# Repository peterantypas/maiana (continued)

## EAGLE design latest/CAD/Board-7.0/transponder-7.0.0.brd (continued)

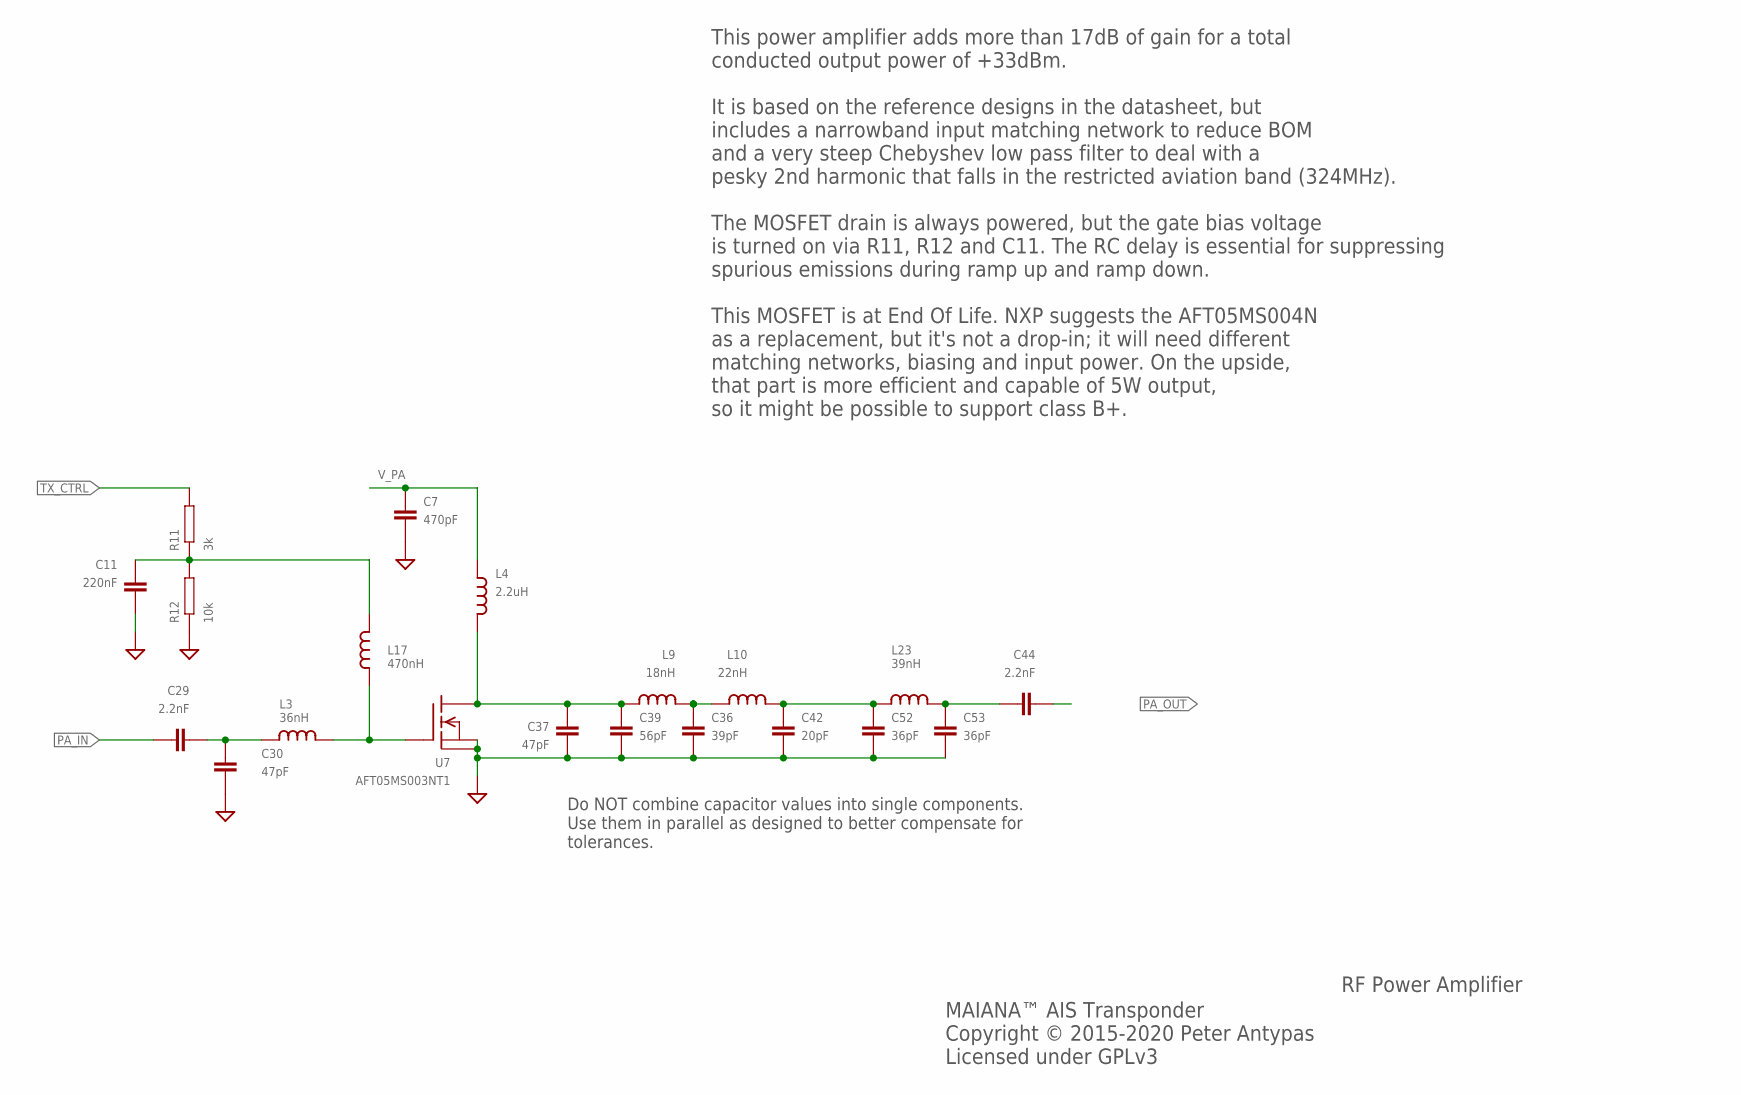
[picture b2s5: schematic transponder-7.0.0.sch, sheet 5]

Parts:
C7: 470pF; 0603; PARTNO GRM1885C1H471JA01D
C11: 220nF; 0603; PARTNO C0603C224K4RECAUTO
C29, C44: 2.2nF; 0603; PARTNO GRM1885C1H222JA01J
C30, C37: 47pF; 0603; PARTNO GRM1885C1H470JA01J
C36: 39pF; 0603; PARTNO GRM1885C1H390JA01D
C39: 56pF; 0603; PARTNO GRM1885C1H560JA01D
C42: 20pF; 0603; PARTNO GRM1885C1H200JA01D
C52, C53: 36pF; 0603; PARTNO 06035A360JAT2A
L3: 36nH; 0603; PARTNO LQW18AN36NG00D
L4: 2.2uH; 0805; PARTNO BRC2012T2R2MD
L9: 18nH; 0603; PARTNO LQW18AN18NG00D
L10: 22nH; 0603; PARTNO LQW18AN22NJ00D
L17: 470nH; 0603; PARTNO HK1608R47J-T
L23: 39nH; 0603; PARTNO LQW18AN39NG00D
R11: 3k; 0603; PARTNO RC0603JR-073KL
R12: 10k; 0603; PARTNO RC0603JR-0710KL
U7: AFT05MS003NT1; SOT-89; PARTNO AFT05MS003NT1

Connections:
GND: C7.P$2 (2), C11.P$2 (2), C30.P$2 (2), C36.P$2 (2), C37.P$2 (2), C39.P$2 (2), C42.P$2 (2), C52.P$2 (2), C53.P$2 (2), R12.P$1, U7.2 (S), U7.2@1 (PAD); also elsewhere on the board
unnamed: C11.P$1 (1), L17.P$2 (2), R11.P$1, R12.P$2
unnamed: C37.P$1 (1), C39.P$1 (1), L4.P$2 (2), L9.P$1 (1), U7.3 (D)
unnamed: L3.P$2 (2), L17.P$1 (1), U7.1 (G)
unnamed: C36.P$1 (1), L9.P$2 (2), L10.P$1 (1)
unnamed: C29.P$2 (2), C30.P$1 (1), L3.P$1 (1)
unnamed: C42.P$1 (1), C52.P$1 (1), L10.P$2 (2), L23.P$1 (1)
unnamed: C44.P$1 (1), C53.P$1 (1), L23.P$2 (2)
PA_IN: C29.P$1 (1); also elsewhere on the board
PA_OUT: C44.P$2 (2); also elsewhere on the board
TX_CTRL: R11.P$2; also elsewhere on the board
V_PA: C7.P$1 (1), L4.P$1 (1); also elsewhere on the board

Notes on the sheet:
RF Power Amplifier
MAIANA™ AIS Transponder Copyright © 2015-2020 Peter Antypas Licensed under GPLv3
This power amplifier adds more than 17dB of gain for a total conducted output power of +33dBm. It is based on the reference designs in the datasheet, but includes a narrowband input matching network to reduce BOM and a very steep Chebyshev low pass filter to deal with a pesky 2nd harmonic that fall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
Do NOT combine capacitor values into single components. Use them in parallel as designed to better compensate for tolerances.

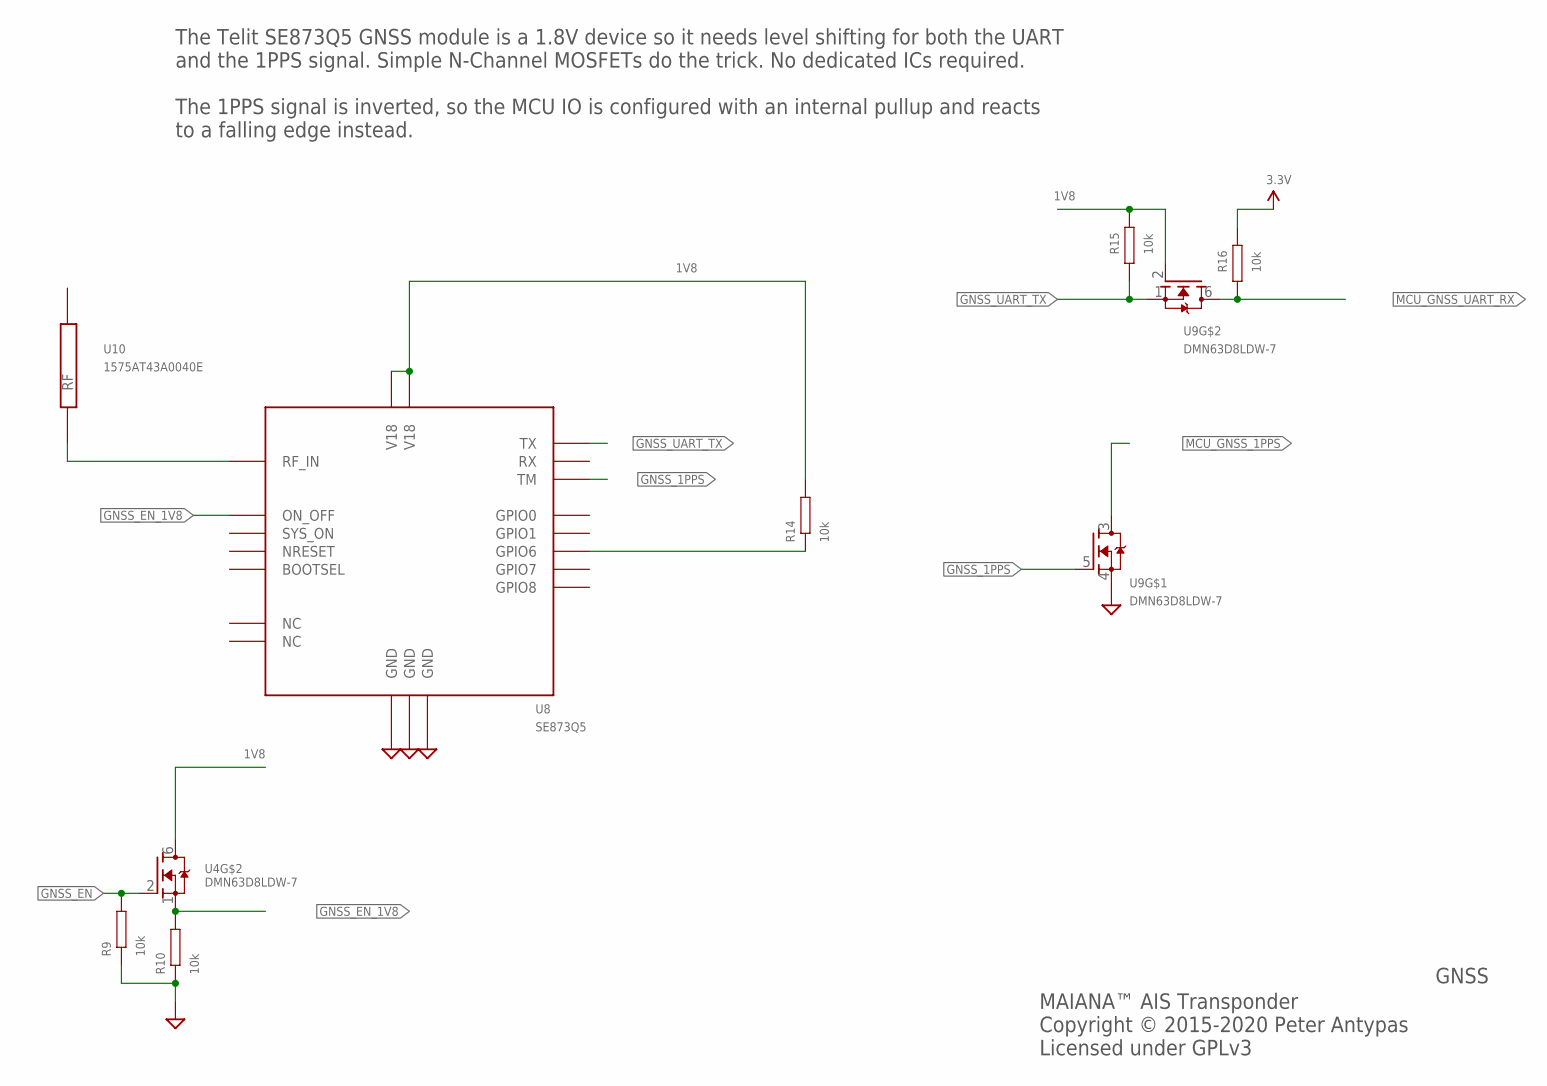
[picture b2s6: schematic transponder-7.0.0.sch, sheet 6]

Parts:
R9, R10, R14, R15, R16: 10k; 0603; PARTNO RC0603JR-0710KL
U4, U9: DMN63D8LDW-7; SOT363; PARTNO DMN63D8LDW-7
U8: SE873Q5; SE873; PARTNO SE873Q5
U10: 1575AT43A0040E; PARTNO 1575AT43A0040E

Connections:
1V8: R14.P$2, R15.P$2, U4.6 (D), U8.P$3 (V18), U8.P$19 (V18), U9.2 (G); also elsewhere on the board
3.3V: R16.P$2; also elsewhere on the board
GND: R9.P$1, R10.P$1, U8.P$2 (GND), U8.P$10 (GND), U8.P$20 (GND), U9.4 (S); also elsewhere on the board
GNSS_1PPS: U8.P$11 (TM), U9.5 (G)
GNSS_EN: R9.P$2, U4.2 (G); also elsewhere on the board
GNSS_EN_1V8: R10.P$2, U4.1 (S), U8.P$6 (ON_OFF)
GNSS_UART_TX: R15.P$1, U8.P$15 (TX), U9.1 (S)
MCU_GNSS_1PPS: U9.3 (D); also elsewhere on the board
MCU_GNSS_UART_RX: R16.P$1, U9.6 (D); also elsewhere on the board
unnamed: U8.P$1 (RF_IN), U10.P$1 (RF)
unnamed: R14.P$1, U8.P$13 (GPIO6)

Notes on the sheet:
GNSS
MAIANA™ AIS Transponder Copyright © 2015-2020 Peter Antypas Licensed under GPLv3
The Telit SE873Q5 GNSS module is a 1.8V device so it needs level shifting for both the UART and the 1PPS signal. Simple N-Channel MOSFETs do the trick. No dedicated ICs required. The 1PPS signal is inverted, so the MCU IO is configured with an internal pullup and reacts to a falling edge instead.

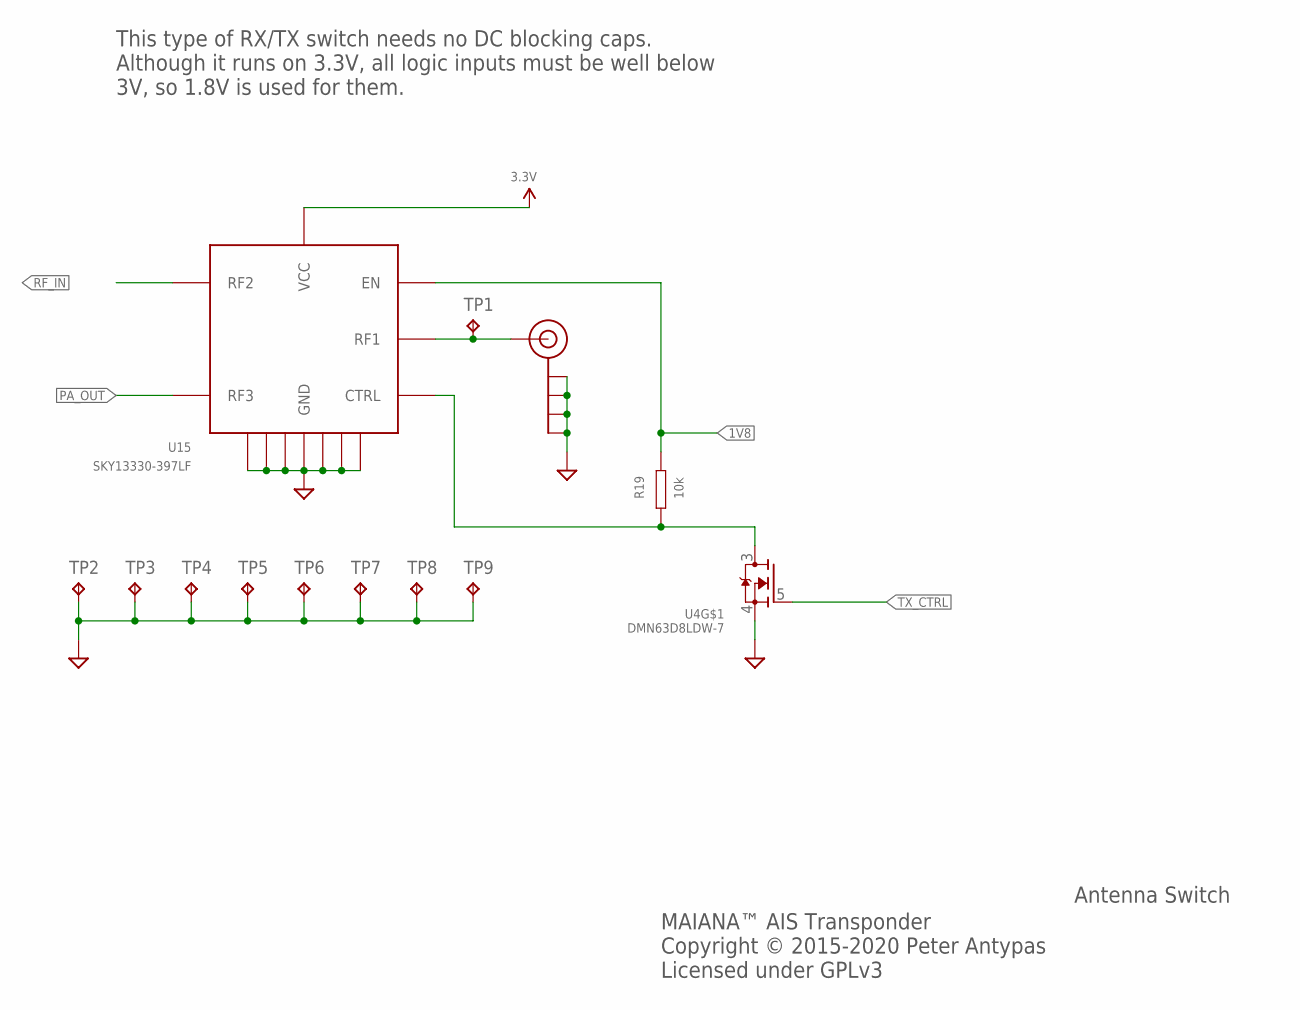
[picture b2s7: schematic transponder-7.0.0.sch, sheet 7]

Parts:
J$1: SMA_EDGE; SMA-EDGE
R19: 10k; 0603; PARTNO RC0603JR-0710KL
TP1: TPTP10R; TP10R
TP2, TP3, TP4, TP5, TP6, TP7, TP8, TP9: TPTP08R; TP08R
U4: DMN63D8LDW-7; SOT363; PARTNO DMN63D8LDW-7
U15: SKY13330-397LF; QFN12; PARTNO SKY13330-397LF

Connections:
1V8: R19.P$2, U15.P$8 (EN); also elsewhere on the board
3.3V: U15.P$9 (VCC); also elsewhere on the board
GND: J$1.GND@0 (GND), J$1.GND@1 (GND), J$1.GND@2 (GND), J$1.GND@3 (GND), TP2.TP, TP3.TP, TP4.TP, TP5.TP, TP6.TP, TP7.TP, TP8.TP, TP9.TP, U4.4 (S), U15.P$1 (GND), U15.P$3 (GND), U15.P$4 (GND), U15.P$6 (GND), U15.P$10 (GND), U15.P$12 (GND), U15.P$13 (GND); also elsewhere on the board
unnamed: J$1.SIG (SIGNAL), TP1.TP, U15.P$2 (RF1)
PA_OUT: U15.P$5 (RF3); also elsewhere on the board
RF_IN: U15.P$11 (RF2); also elsewhere on the board
RX_EN: R19.P$1, U4.3 (D), U15.P$7 (CTRL)
TX_CTRL: U4.5 (G); also elsewhere on the board

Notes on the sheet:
Antenna Switch
MAIANA™ AIS Transponder Copyright © 2015-2020 Peter Antypas Licensed under GPLv3
This type of RX/TX switch needs no DC blocking caps. Although it runs on 3.3V, all logic inputs must be well below 3V, so 1.8V is used for them.

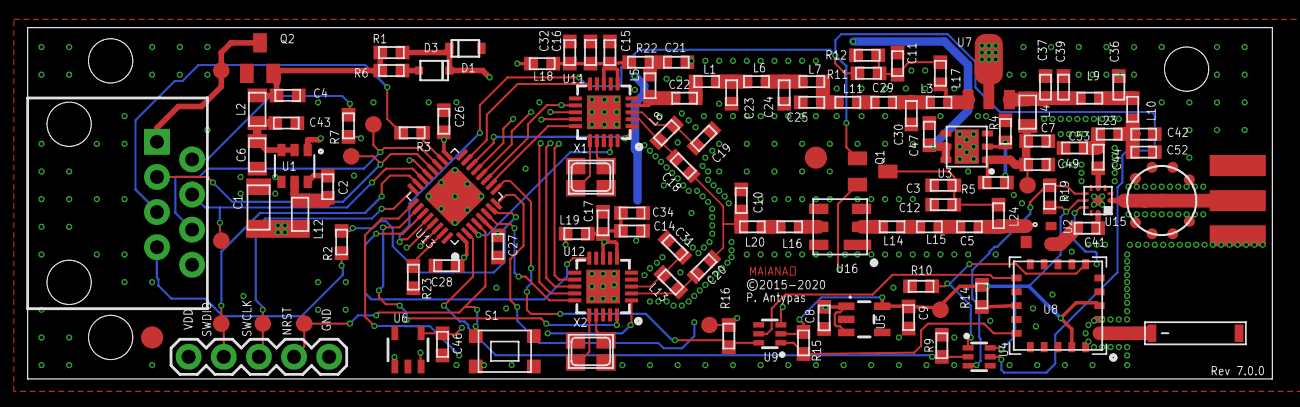
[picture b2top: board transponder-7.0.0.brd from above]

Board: 4 copper layers, 90.0 x 25.4 mm, 130 parts (1 on the bottom side), 84 nets.

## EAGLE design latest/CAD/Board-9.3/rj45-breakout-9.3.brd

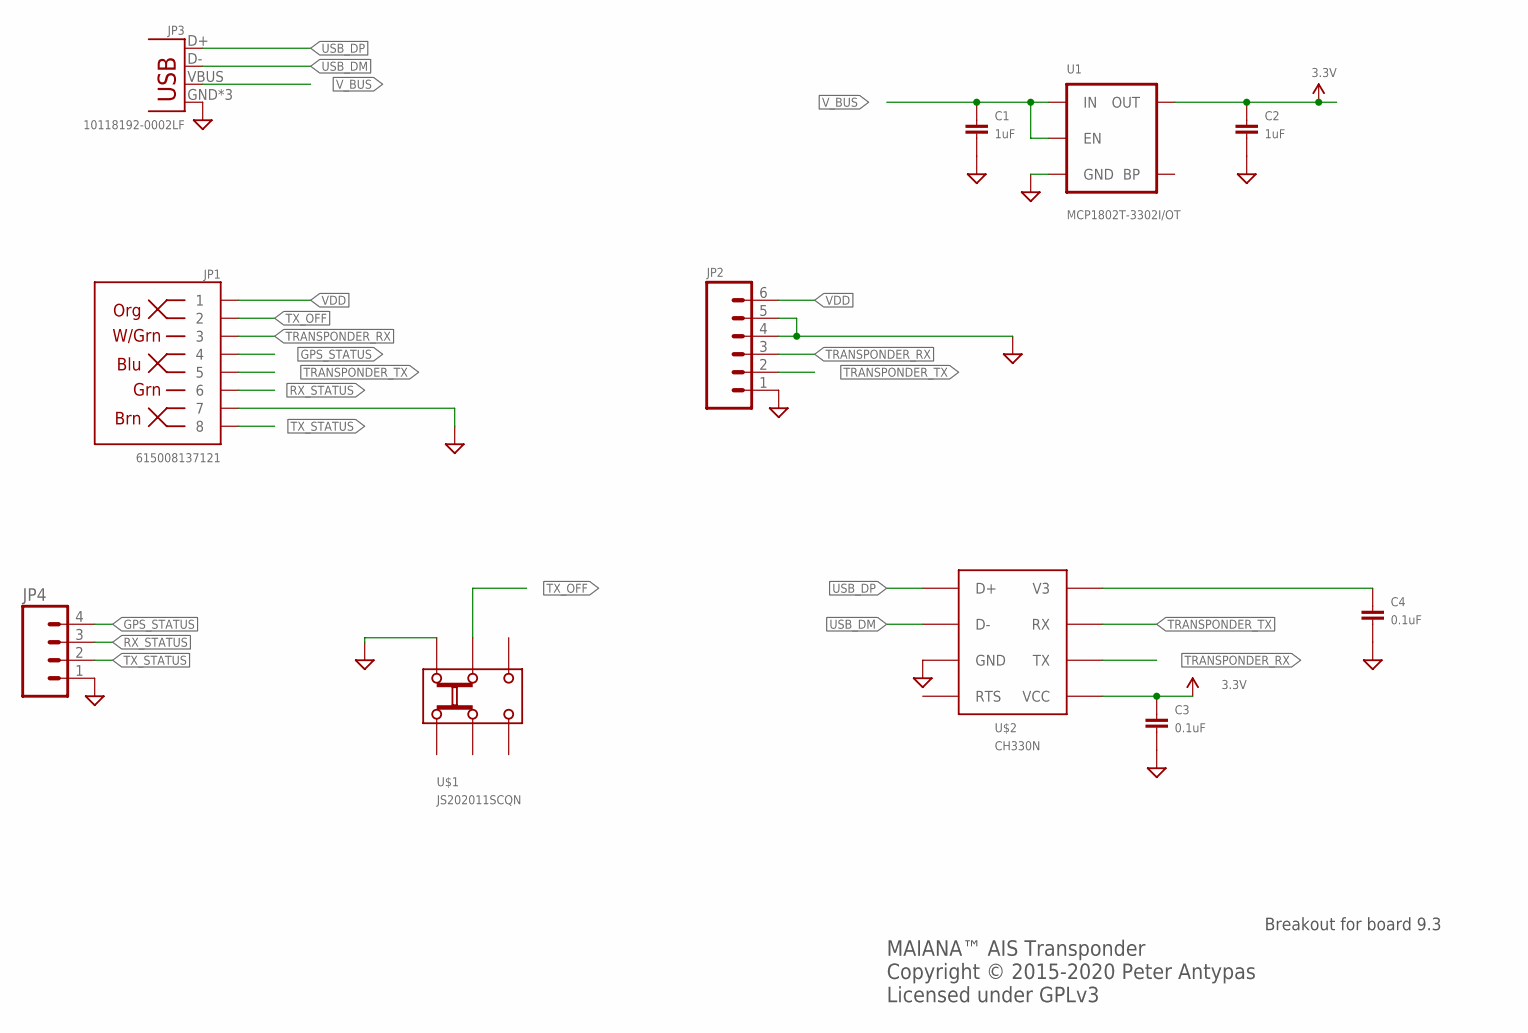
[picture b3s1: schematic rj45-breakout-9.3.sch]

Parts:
C1, C2: 1uF; 0603
C3, C4: 0.1uF; 0603
JP1: 615008137121; RJ45-8
JP2: M06SILK_FEMALE_PTH; 1X06
JP3: 10118192-0002LF; USB-MICROB
JP4: M04PTH; 1X04
U1: MCP1802T-3302I/OT; SOT23-5
U$1: JS202011SCQN; DPDT-SMD
U$2: CH330N; SOIC-8

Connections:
3.3V: C2.P$1, C3.P$1, U1.5 (OUT), U$2.5 (VCC)
GND: C1.P$2, C2.P$2, C3.P$2, C4.P$2, JP1.7, JP2.1, JP2.4, JP2.5, JP3.GND, JP3.MT1 (GND), JP3.MT2 (GND), JP4.1, U1.2 (GND), U$1.P$6, U$2.3 (GND)
GPS_STATUS: JP1.4, JP4.4
unnamed: C4.P$1, U$2.8 (V3)
RX_STATUS: JP1.6, JP4.3
TRANSPONDER_RX: JP1.3, JP2.3, U$2.6 (TX)
TRANSPONDER_TX: JP1.5, JP2.2, U$2.7 (RX)
TX_OFF: JP1.2, U$1.P$5
TX_STATUS: JP1.8, JP4.2
USB_DM: JP3.D-, U$2.2 (D-)
USB_DP: JP3.D+, U$2.1 (D+)
VDD: JP1.1, JP2.6
V_BUS: C1.P$1, JP3.VBUS, U1.1 (IN), U1.3 (EN)

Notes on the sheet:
MAIANA™ AIS Transponder Copyright © 2015-2020 Peter Antypas Licensed under GPLv3
Breakout for board 9.3

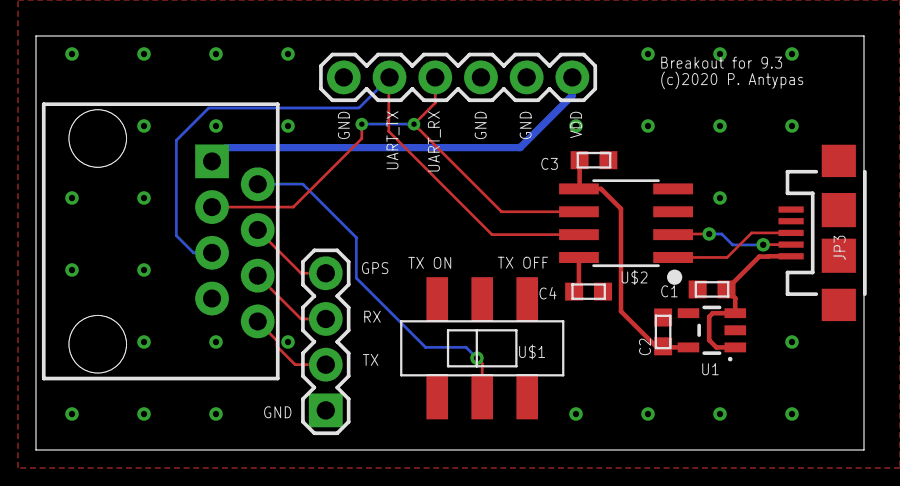
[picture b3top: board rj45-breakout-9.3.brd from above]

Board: 2 copper layers, 46.0 x 23.0 mm, 11 parts (0 on the bottom side), 13 nets.

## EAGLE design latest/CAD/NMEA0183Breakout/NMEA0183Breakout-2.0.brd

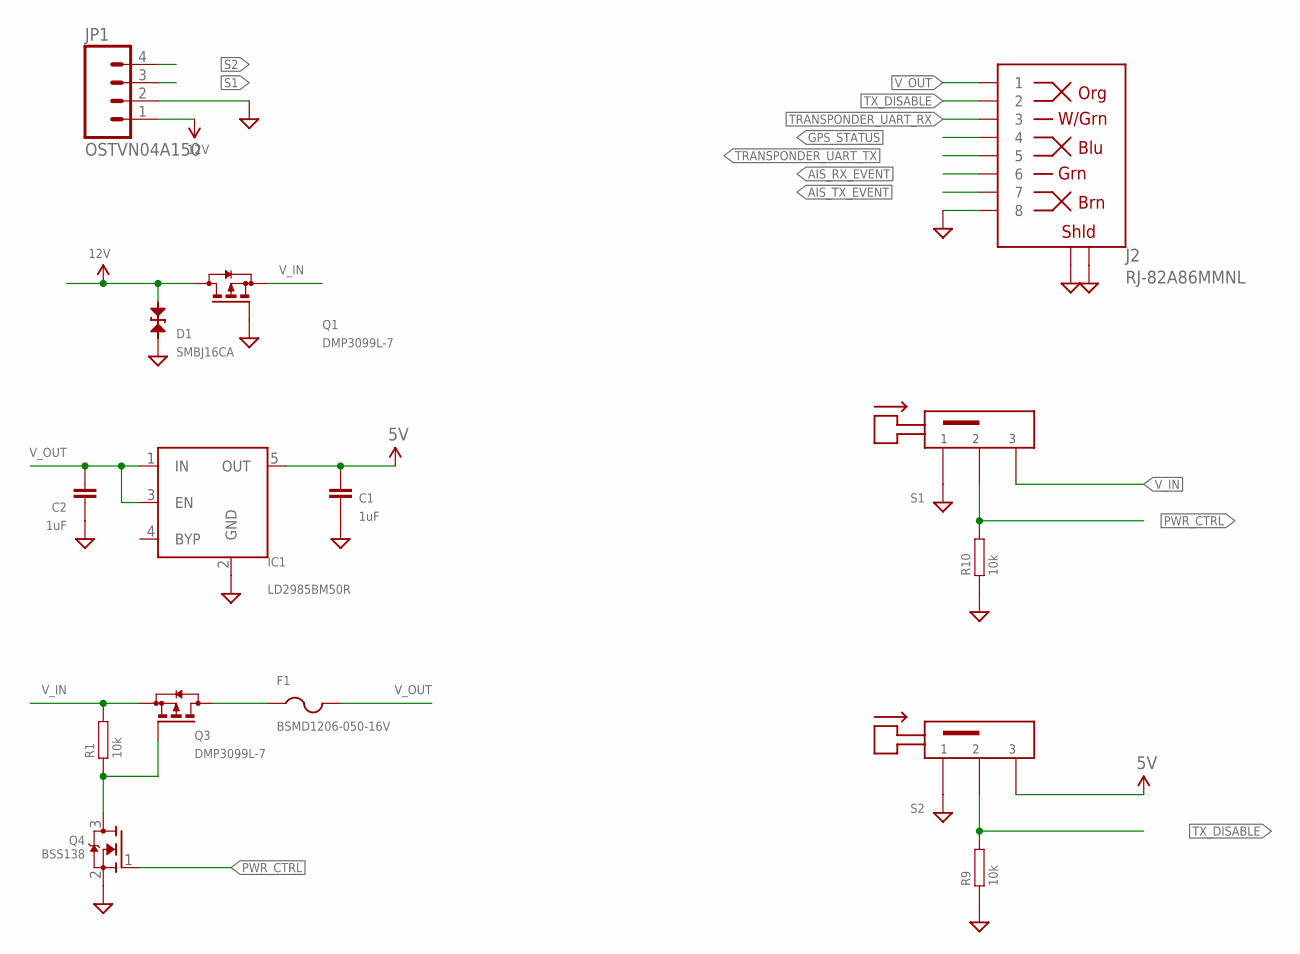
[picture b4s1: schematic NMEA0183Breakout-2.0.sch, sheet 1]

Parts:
C1, C2: 1uF; 0603
D1: SMBJ16CA; SMB-BIDIR
F1: BSMD1206-050-16V; R1206
IC1: LD2985BM50R; SOT23-5
J2: RJ-82A86MMNL
JP1: OSTVN04A150; 1X04
Q1, Q3: DMP3099L-7; SOT23
Q4: BSS138; SOT23
R1, R9, R10: 10k; 0603
S1, S2: LC1258XXNP

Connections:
5V: C1.P$1 (1), IC1.5 (OUT), S2.P$3 (3); also elsewhere on the board
12V: D1.A, JP1.1, Q1.3 (D)
AIS_RX_EVENT: J2.P$6 (6); also elsewhere on the board
AIS_TX_EVENT: J2.P$7 (7); also elsewhere on the board
GND: C1.P$2 (2), C2.P$2 (2), D1.C, IC1.2 (GND), J2.P$8 (8), J2.P$9 (SHLD), J2.P$10 (SHLD), J2.P$11 (SHLD), J2.P$12 (SHLD), JP1.2, Q1.1 (G), Q4.2 (S), R9.P$1, R10.P$1, S1.P$1 (1), S2.P$1 (1); also elsewhere on the board
GPS_STATUS: J2.P$4 (4); also elsewhere on the board
unnamed: Q3.1 (G), Q4.3 (D), R1.P$1
unnamed: F1.1, Q3.3 (D)
PWR_CTRL: Q4.1 (G), R10.P$2, S1.P$2 (2)
S1: JP1.3; also elsewhere on the board
S2: JP1.4; also elsewhere on the board
TRANSPONDER_UART_RX: J2.P$3 (3); also elsewhere on the board
TRANSPONDER_UART_TX: J2.P$5 (5); also elsewhere on the board
TX_DISABLE: J2.P$2 (2), R9.P$2, S2.P$2 (2); also elsewhere on the board
V_IN: Q1.2 (S), Q3.2 (S), R1.P$2, S1.P$3 (3)
V_OUT: C2.P$1 (1), F1.2, IC1.1 (IN), IC1.3 (EN), J2.P$1 (1)

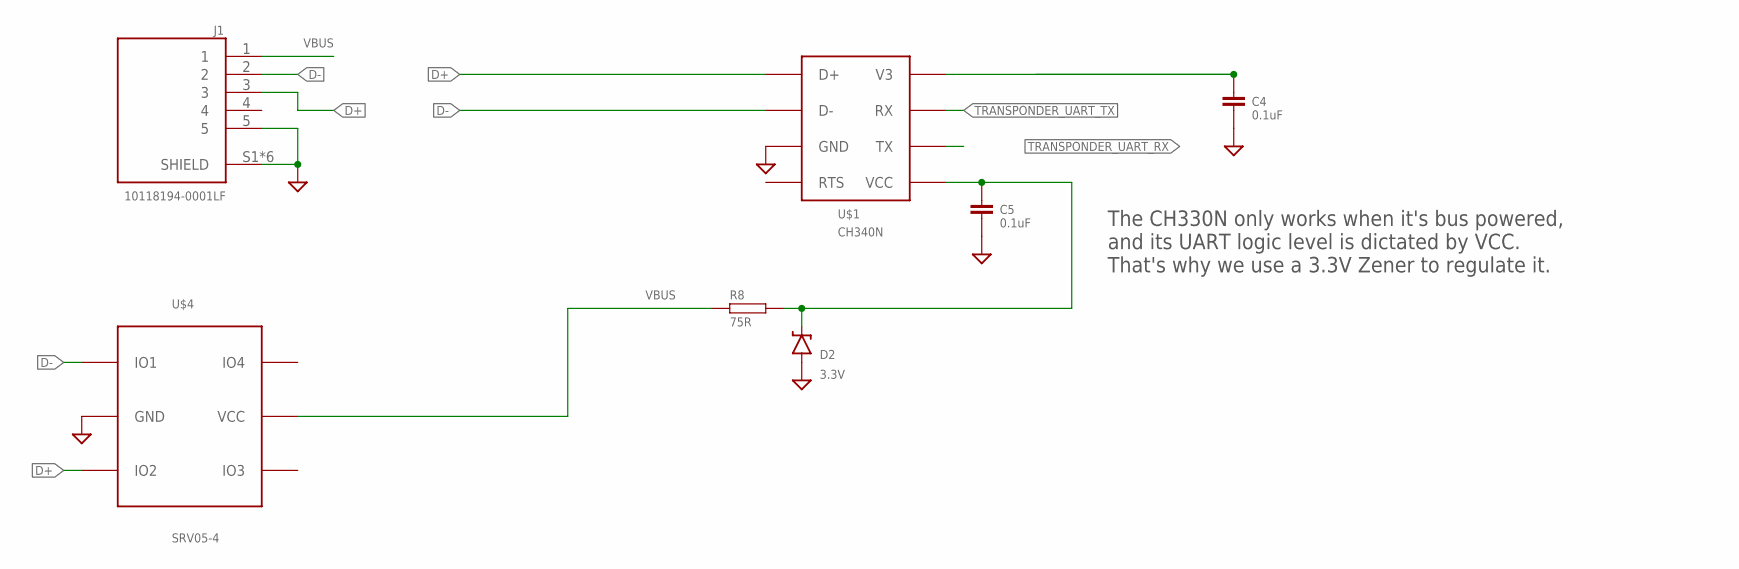
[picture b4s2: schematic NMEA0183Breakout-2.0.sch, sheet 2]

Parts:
C4, C5: 0.1uF; 0603
D2: 3.3V; SOD-323
J1: 10118194-0001LF; AMPHENOL_10118194-0001LF
R8: 75R; 0603
U$1: CH340N; SOIC-8; PARTNO CH340N
U$4: SRV05-4; SOT23-6

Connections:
D+: J1.3, U$1.1 (D+), U$4.3 (IO2)
D-: J1.2, U$1.2 (D-), U$4.1 (IO1)
GND: C4.P$2 (2), C5.P$2 (2), D2.A, J1.5, J1.S1 (SHIELD), J1.S2 (SHIELD), J1.S3 (SHIELD), J1.S4 (SHIELD), J1.S5 (SHIELD), J1.S6 (SHIELD), U$1.3 (GND), U$4.2 (GND); also elsewhere on the board
unnamed: C4.P$1 (1), U$1.8 (V3)
unnamed: C5.P$1 (1), D2.C, R8.P$2, U$1.5 (VCC)
TRANSPONDER_UART_RX: U$1.6 (TX); also elsewhere on the board
TRANSPONDER_UART_TX: U$1.7 (RX); also elsewhere on the board
VBUS: J1.1, R8.P$1, U$4.5 (VCC)

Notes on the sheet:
The CH330N only works when it's bus powered, and its UART logic level is dictated by VCC. That's why we use a 3.3V Zener to regulate it.

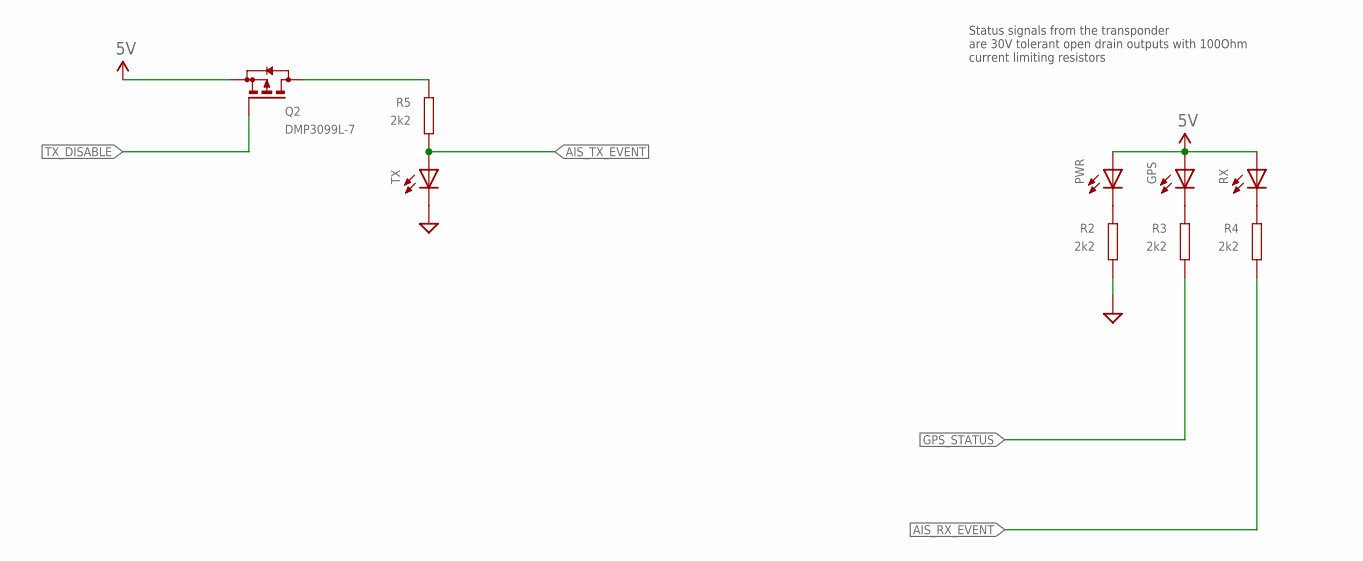
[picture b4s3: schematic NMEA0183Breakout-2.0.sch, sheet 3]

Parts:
GPS: LEDCHIPLED_1206; CHIPLED_1206; PARTNO TJ-S3216CL9T5ALC2G-A5
PWR: LEDCHIPLED_1206; CHIPLED_1206; PARTNO TJ-S3216CL9T5ALC2G-A5
Q2: DMP3099L-7; SOT23
R2, R3, R4, R5: 2k2; 0603
RX: LEDCHIPLED_1206; CHIPLED_1206; PARTNO TJ-S3216CL9T5ALC2G-A5
TX: LEDCHIPLED_1206; CHIPLED_1206; PARTNO TJ-S3216CL9T5ALC2G-A5

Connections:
5V: GPS.A, PWR.A, Q2.2 (S), RX.A; also elsewhere on the board
AIS_RX_EVENT: R4.P$2; also elsewhere on the board
AIS_TX_EVENT: R5.P$2, TX.A; also elsewhere on the board
GND: R2.P$2, TX.C; also elsewhere on the board
GPS_STATUS: R3.P$2; also elsewhere on the board
unnamed: PWR.C, R2.P$1
unnamed: GPS.C, R3.P$1
unnamed: R4.P$1, RX.C
unnamed: Q2.3 (D), R5.P$1
TX_DISABLE: Q2.1 (G); also elsewhere on the board

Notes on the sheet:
Status signals from the transponder are 30V tolerant open drain outputs with 100Ohm current limiting resistors

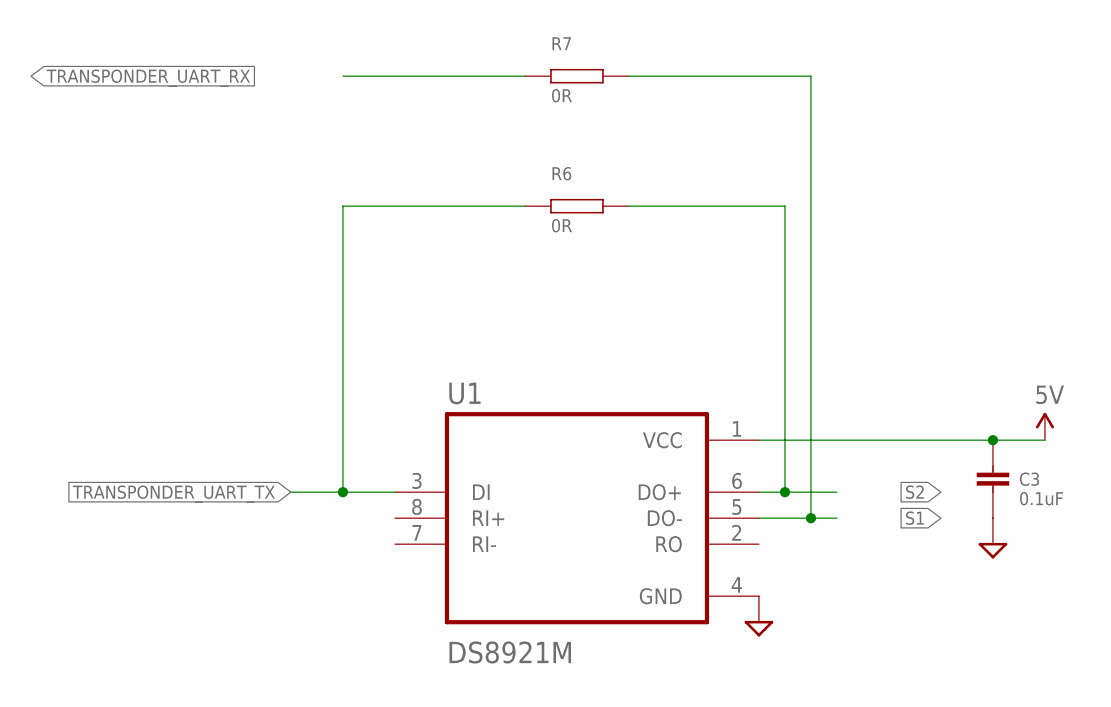
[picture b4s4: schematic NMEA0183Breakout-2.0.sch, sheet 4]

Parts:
C3: 0.1uF; 0603
R6, R7: 0R; 0603
U1: DS8921M; SOIC127P599X175-8N

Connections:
5V: C3.P$1 (1), U1.1 (VCC); also elsewhere on the board
GND: C3.P$2 (2), U1.4 (GND); also elsewhere on the board
S1: R7.P$2, U1.5 (DO-); also elsewhere on the board
S2: R6.P$2, U1.6 (DO+); also elsewhere on the board
TRANSPONDER_UART_RX: R7.P$1; also elsewhere on the board
TRANSPONDER_UART_TX: R6.P$1, U1.3 (DI); also elsewhere on the board

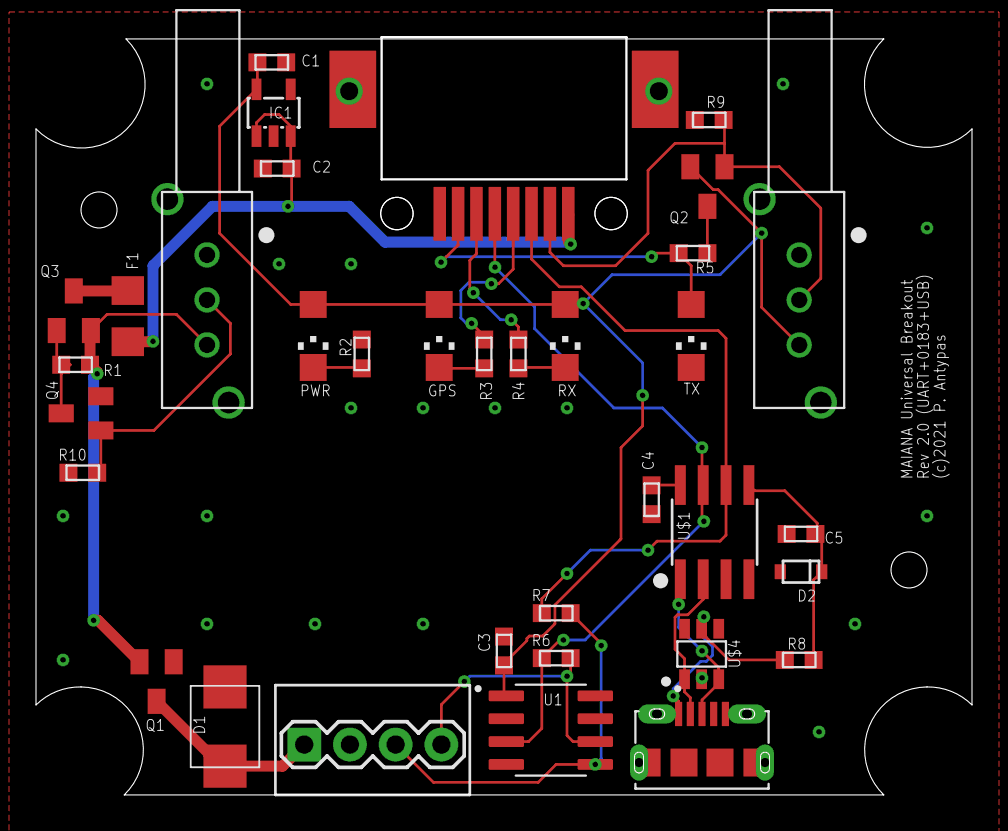
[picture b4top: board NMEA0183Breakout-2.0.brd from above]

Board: 2 copper layers, 52.0 x 42.0 mm, 35 parts (0 on the bottom side), 25 nets.

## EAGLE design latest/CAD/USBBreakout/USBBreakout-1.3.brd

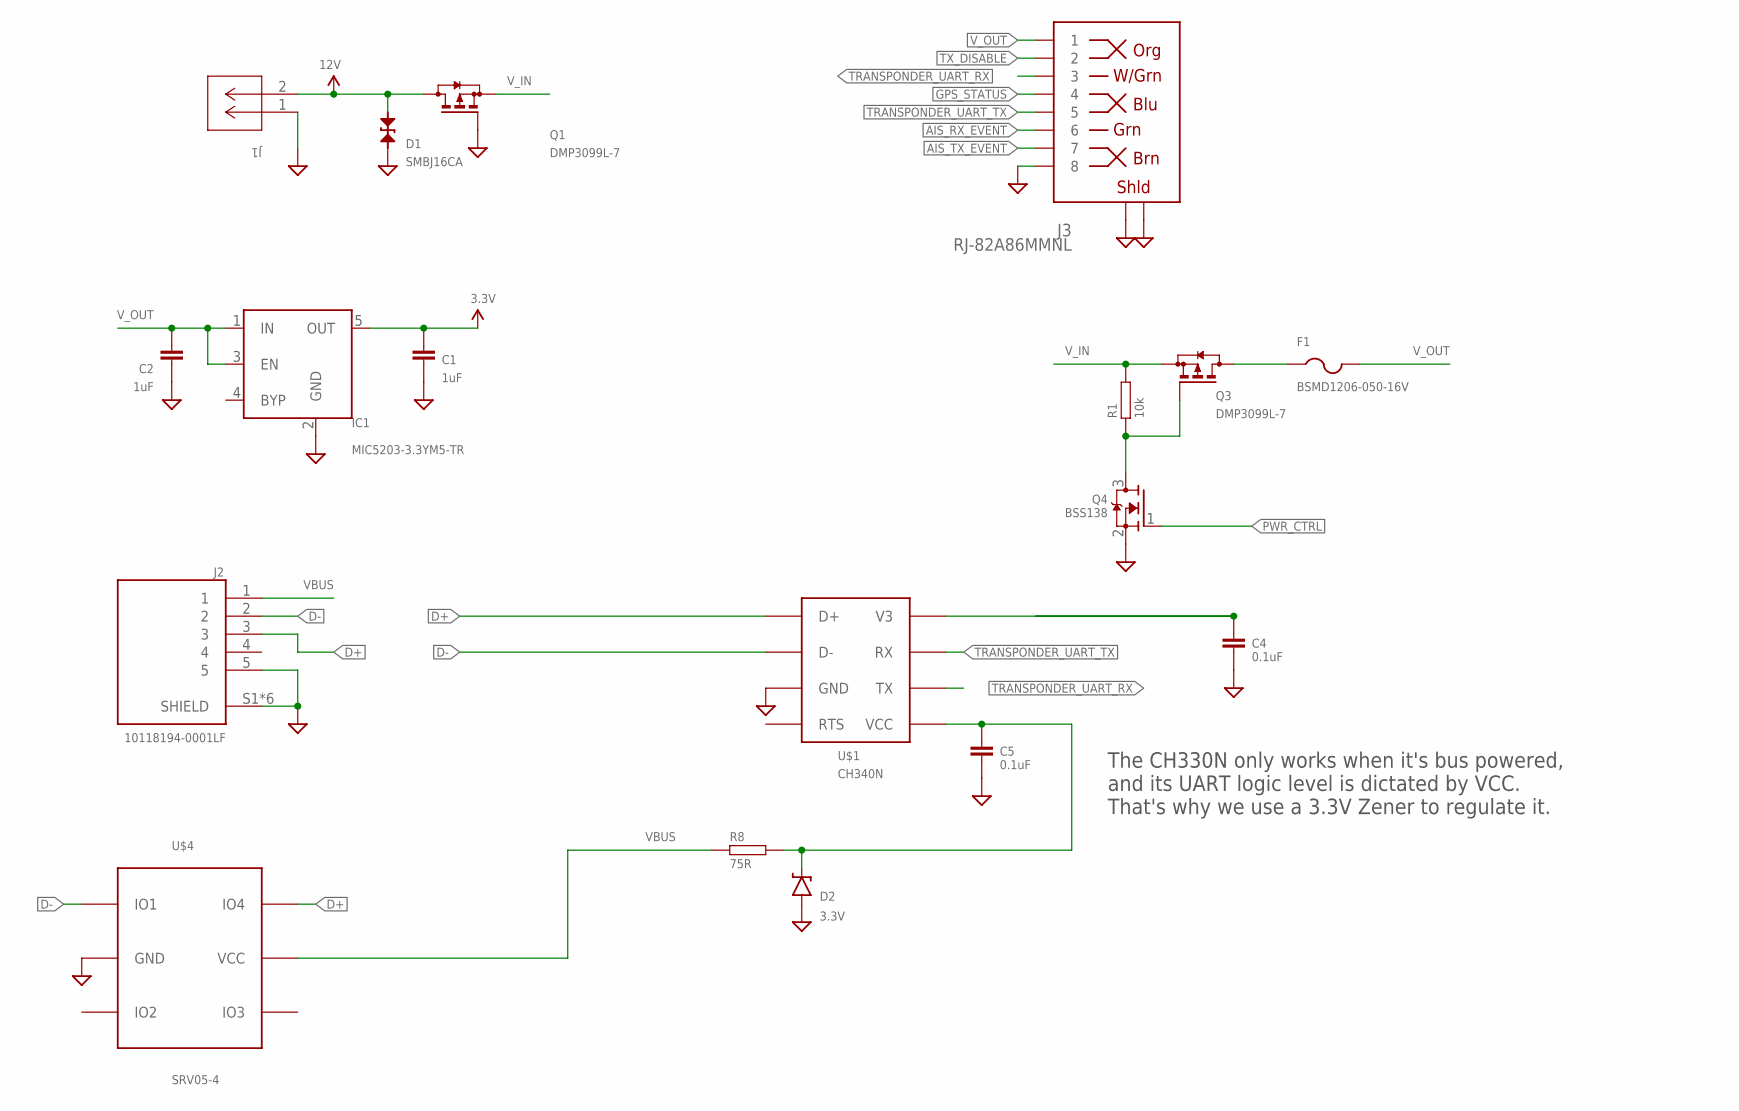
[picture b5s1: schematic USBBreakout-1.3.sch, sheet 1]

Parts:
C1, C2: 1uF; 0603
C4, C5: 0.1uF; 0603
D1: SMBJ16CA; SMB-BIDIR
D2: 3.3V; SOD-323
F1: BSMD1206-050-16V; R1206
IC1: MIC5203-3.3YM5-TR; SOT23-5
J1: OSTVN02A150; CONN_OSTVN02A150_OST
J2: 10118194-0001LF; AMPHENOL_10118194-0001LF
J3: RJ-82A86MMNL
Q1, Q3: DMP3099L-7; SOT23
Q4: BSS138; SOT23
R1: 10k; 0603
R8: 75R; 0603
U$1: CH340N; SOIC-8; PARTNO CH340N
U$4: SRV05-4; SOT23-6

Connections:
3.3V: C1.P$1 (1), IC1.5 (OUT); also elsewhere on the board
12V: D1.A, J1.2, Q1.3 (D)
AIS_RX_EVENT: J3.P$6 (6); also elsewhere on the board
AIS_TX_EVENT: J3.P$7 (7); also elsewhere on the board
D+: J2.3, U$1.1 (D+), U$4.6 (IO4)
D-: J2.2, U$1.2 (D-), U$4.1 (IO1)
GND: C1.P$2 (2), C2.P$2 (2), C4.P$2 (2), C5.P$2 (2), D1.C, D2.A, IC1.2 (GND), J1.1, J2.5, J2.S1 (SHIELD), J2.S2 (SHIELD), J2.S3 (SHIELD), J2.S4 (SHIELD), J2.S5 (SHIELD), J2.S6 (SHIELD), J3.P$8 (8), J3.P$9 (SHLD), J3.P$10 (SHLD), J3.P$11 (SHLD), J3.P$12 (SHLD), Q1.1 (G), Q4.2 (S), U$1.3 (GND), U$4.2 (GND); also elsewhere on the board
GPS_STATUS: J3.P$4 (4); also elsewhere on the board
unnamed: C4.P$1 (1), U$1.8 (V3)
unnamed: Q3.1 (G), Q4.3 (D), R1.P$1
unnamed: F1.1, Q3.3 (D)
unnamed: C5.P$1 (1), D2.C, R8.P$2, U$1.5 (VCC)
PWR_CTRL: Q4.1 (G); also elsewhere on the board
TRANSPONDER_UART_RX: J3.P$3 (3), U$1.6 (TX)
TRANSPONDER_UART_TX: J3.P$5 (5), U$1.7 (RX)
TX_DISABLE: J3.P$2 (2); also elsewhere on the board
VBUS: J2.1, R8.P$1, U$4.5 (VCC)
V_IN: Q1.2 (S), Q3.2 (S), R1.P$2; also elsewhere on the board
V_OUT: C2.P$1 (1), F1.2, IC1.1 (IN), IC1.3 (EN), J3.P$1 (1)

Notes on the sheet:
The CH330N only works when it's bus powered, and its UART logic level is dictated by VCC. That's why we use a 3.3V Zener to regulate it.

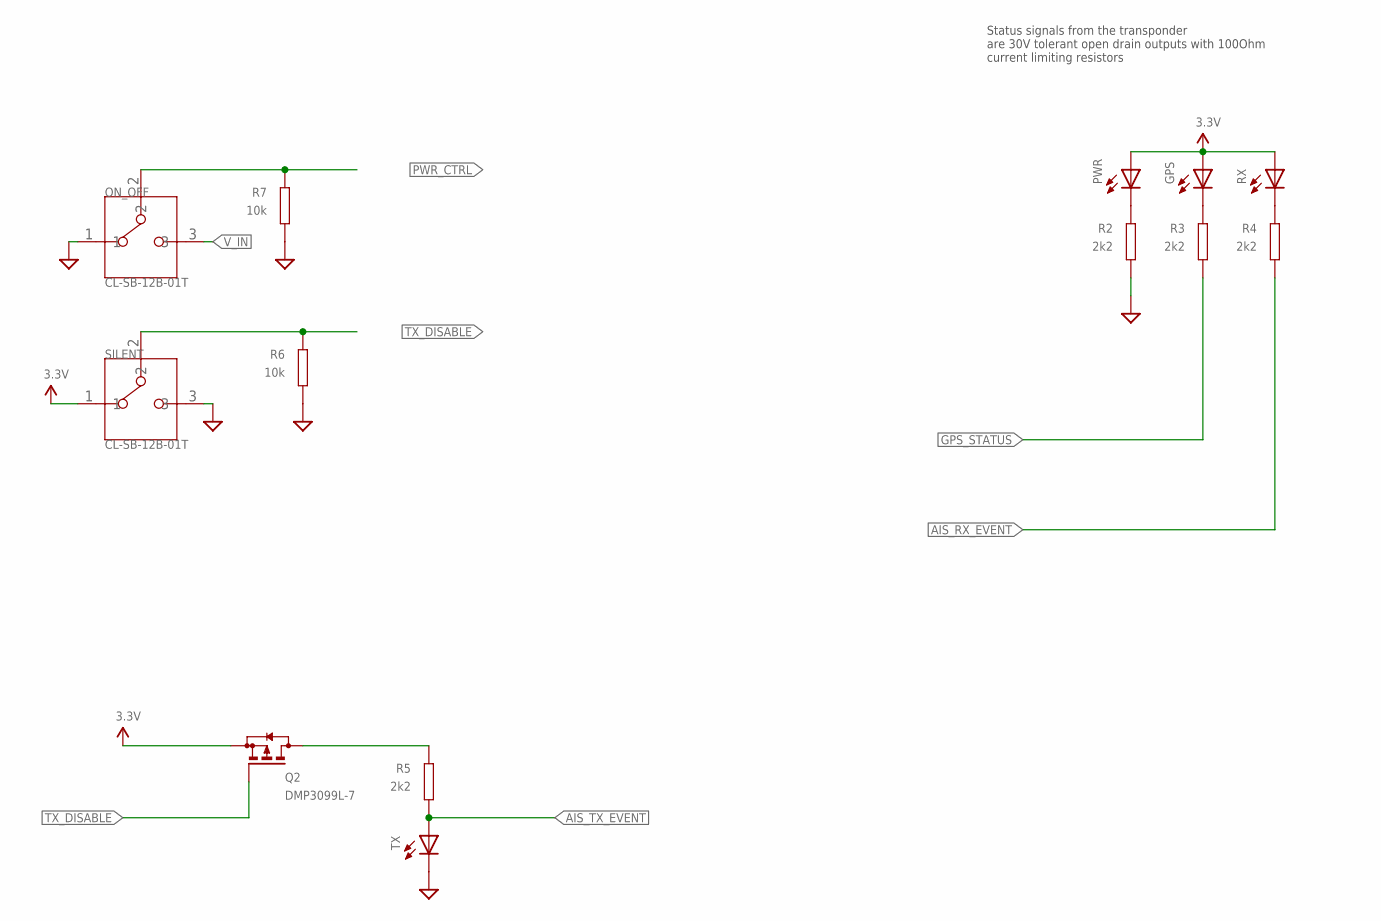
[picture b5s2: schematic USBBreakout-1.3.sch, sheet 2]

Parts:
GPS: LEDCHIPLED_1206; CHIPLED_1206; PARTNO TJ-S3216CL9T5ALC2G-A5
ON_OFF: CL-SB-12B-01T; CL-SB-12B
PWR: LEDCHIPLED_1206; CHIPLED_1206; PARTNO TJ-S3216CL9T5ALC2G-A5
Q2: DMP3099L-7; SOT23
R2, R3, R4, R5: 2k2; 0603
R6, R7: 10k; 0603
RX: LEDCHIPLED_1206; CHIPLED_1206; PARTNO TJ-S3216CL9T5ALC2G-A5
SILENT: CL-SB-12B-01T; CL-SB-12B
TX: LEDCHIPLED_1206; CHIPLED_1206; PARTNO TJ-S3216CL9T5ALC2G-A5

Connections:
3.3V: GPS.A, PWR.A, Q2.2 (S), RX.A, SILENT.1; also elsewhere on the board
AIS_RX_EVENT: R4.P$2; also elsewhere on the board
AIS_TX_EVENT: R5.P$2, TX.A; also elsewhere on the board
GND: ON_OFF.1, R2.P$2, R6.P$2, R7.P$2, SILENT.3, TX.C; also elsewhere on the board
GPS_STATUS: R3.P$2; also elsewhere on the board
unnamed: PWR.C, R2.P$1
unnamed: GPS.C, R3.P$1
unnamed: R4.P$1, RX.C
unnamed: Q2.3 (D), R5.P$1
PWR_CTRL: ON_OFF.2, R7.P$1; also elsewhere on the board
TX_DISABLE: Q2.1 (G), R6.P$1, SILENT.2; also elsewhere on the board
V_IN: ON_OFF.3; also elsewhere on the board

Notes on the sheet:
Status signals from the transponder are 30V tolerant open drain outputs with 100Ohm current limiting resistors
